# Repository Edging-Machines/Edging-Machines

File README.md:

This repository is a hub of information for [Edging Detection](https://github.com/Edging-Machines/Edging-Machines/wiki/Terminology#edging-detection) and [Edging Machines](https://github.com/Edging-Machines/Edging-Machines/wiki/Terminology#edging-machine). 
To get started, check the [Quick Start Guide](https://github.com/Edging-Machines/Edging-Machines/wiki), read the [History of Edging Devices](https://github.com/Edging-Machines/Edging-Machines/wiki/History), or browse through the different projects.

For any questions or discussion, please visit the [official discord server for Edging Machines](https://discord.gg/EvYbZBf).

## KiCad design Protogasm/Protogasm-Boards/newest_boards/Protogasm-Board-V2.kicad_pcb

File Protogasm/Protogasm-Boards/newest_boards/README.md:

# Protogasm Board V3

## Changelog

- Solved the issue with the incorrectly positioned SW1. SW1 should now line up with the case correctly (if I did all my math correctly)
- After a ton of problem solving, figured out a place for the MPX5050GP which should allow it to be used on the board without modifying the board. The constraints that I was considering ended up on User.1 and User.2 layers for future reference. The best solution seemed to be having the pressure sensor rotated and placed in the area of the Arduino without a bunch of tall components, with the valve facing the cutout of the case.
- I had hoped to keep most positions in the same place for this update (just fixing SW1 and MPX5050GP), but after moving the MPX I was forced to essentially update the positions of nearly every component. Additionally, I took the liberty of moving the motor pins closer to the case cutout and also flipped them to the reverse side.

# Protogasm Board V2

## Changelog

- Recreated the PCB from the Protogasm-Board folder in Kicad with only very minor changes.
- The vast majority of components are exactly lined up with the existing board. I overlaid the existing board's Gerbers with the gerbers of the remake and adjusted positions until stuff matched exactly.
- The general components C1, D1, SW1, and R1 have slightly different footprints because I was using the Kicad builtin footprints. They aren't pixel perfect but still overall in the same positions.
- I didn't want to just have loose pins for the motor connections and neopixel connections so I created actual components for them, this means I had to move them so that's one thing that has changed significantly in this board.
- Added the Arduino mounting holes, mostly so that it will be easier to test alignment of this board and the case.
- Overall, the idea is that if someone wants to change the Protogasm-Board but doesn't want the other changes that I'd like to make, they could start from this commit.

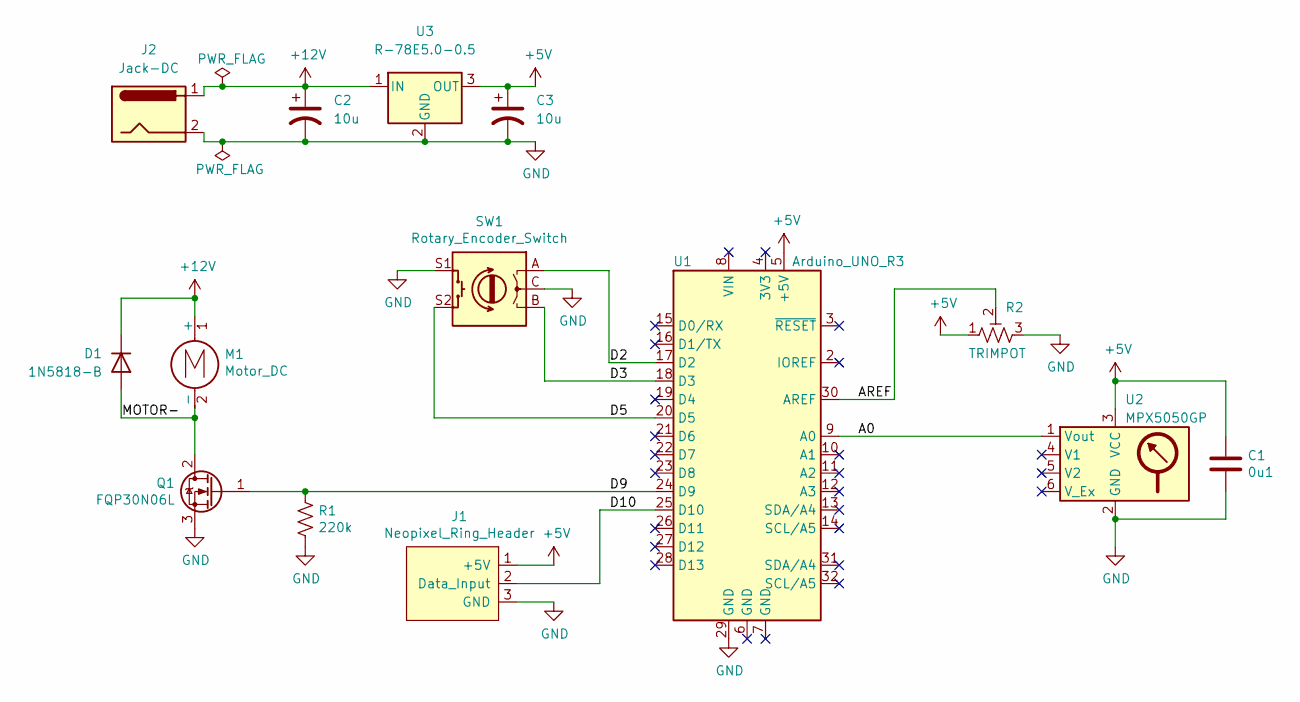
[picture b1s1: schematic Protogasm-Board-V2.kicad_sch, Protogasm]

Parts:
C1: 0u1; C_Disc_D5.0mm_W2.5mm_P2.50mm
C2, C3: 10u; CP_Radial_D5.0mm_P2.50mm
D1: 1N5818-B; D_A-405_P7.62mm_Horizontal
J1: Neopixel_Ring_Header; Neopixel_Ring_WirePins
J2: Jack-DC; 2.1mm DC Barrel Jack
M1: Motor_DC; Motor_DC_WirePins
Q1: FQP30N06L; TO-220-3_Horizontal_TabDown
R1: 220k; R_Axial_DIN0207_L6.3mm_D2.5mm_P7.62mm_Horizontal
R2: TRIMPOT; uxcell_TRIMPOT
SW1: Rotary_Encoder_Switch; RotaryEncoder_Alps_EC12E-Switch_Vertical_H20mm
U1: Arduino_UNO_R3; Arduino_UNO_R3_WithMountingHoles
U2: MPX5050GP
U3: R-78E5.0-0.5; Converter_DCDC_RECOM_R-78E-0.5_THT

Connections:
+5V: C1.1, C3.1, J1.1 (+5V), R2.1, U1.5 (+5V), U2.3 (VCC), U3.3 (OUT)
+12V: C2.1, D1.1 (K), J2.1, M1.1 (+), U3.1 (IN)
/A0: U1.9 (A0), U2.1 (Vout)
/AREF: R2.2, U1.30 (AREF)
/D2: SW1.A, U1.17 (D2)
/D3: SW1.B, U1.18 (D3)
/D5: SW1.S2, U1.20 (D5)
/D9: Q1.1 (G), R1.1, U1.24 (D9)
/D10: J1.2 (Data_Input), U1.25 (D10)
/MOTOR-: D1.2 (A), M1.2 (-), Q1.2 (D)
GND: C1.2, C2.2, C3.2, J1.3 (GND), J2.2, Q1.3 (S), R1.2, R2.3, SW1.C, SW1.S1, U1.29 (GND), U2.2 (GND), U3.2 (GND)

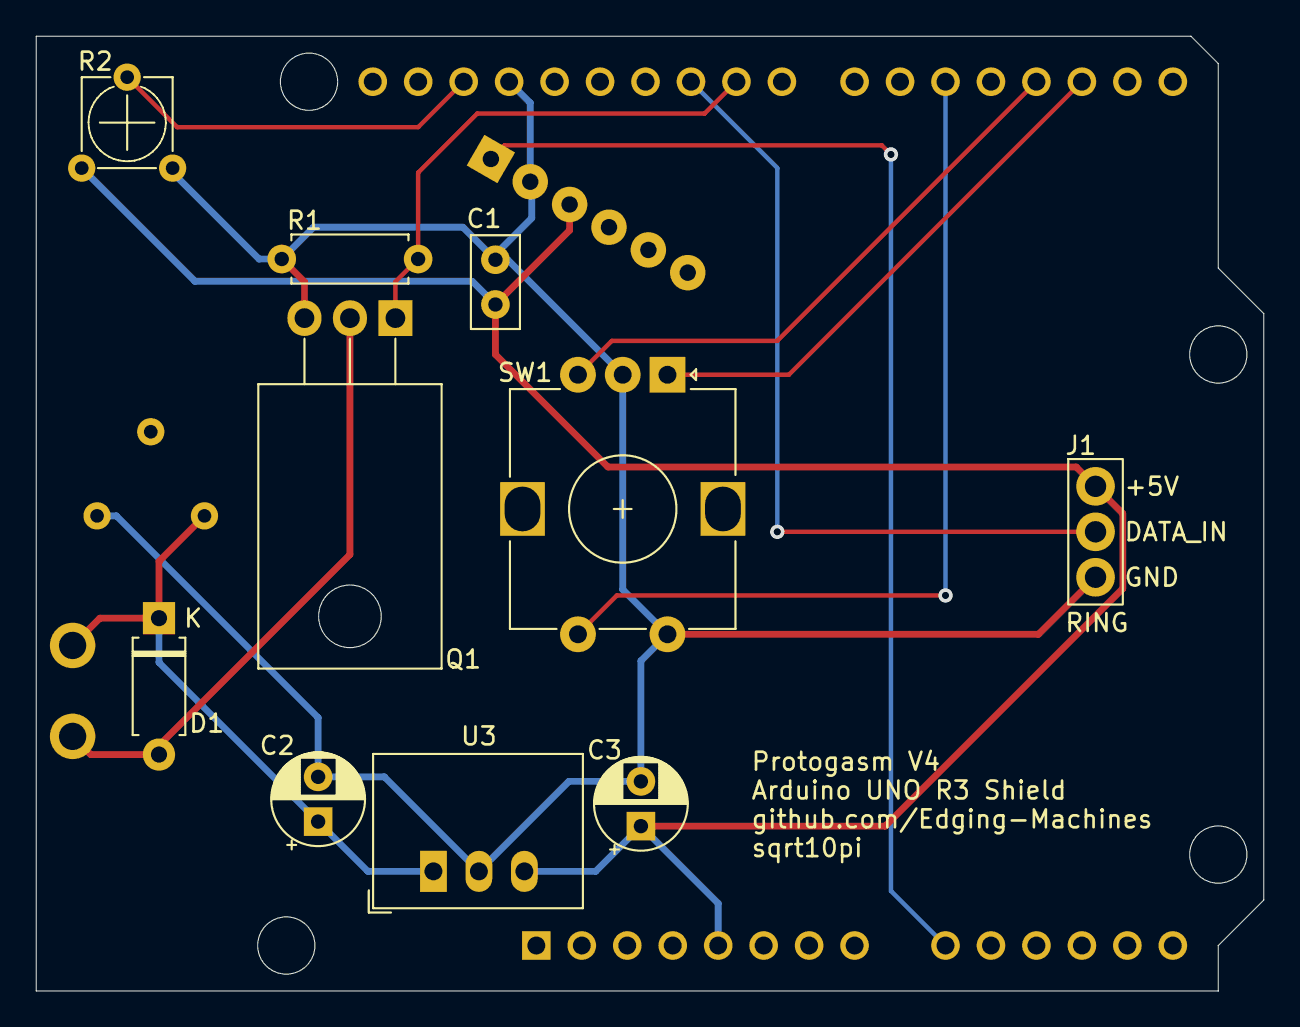
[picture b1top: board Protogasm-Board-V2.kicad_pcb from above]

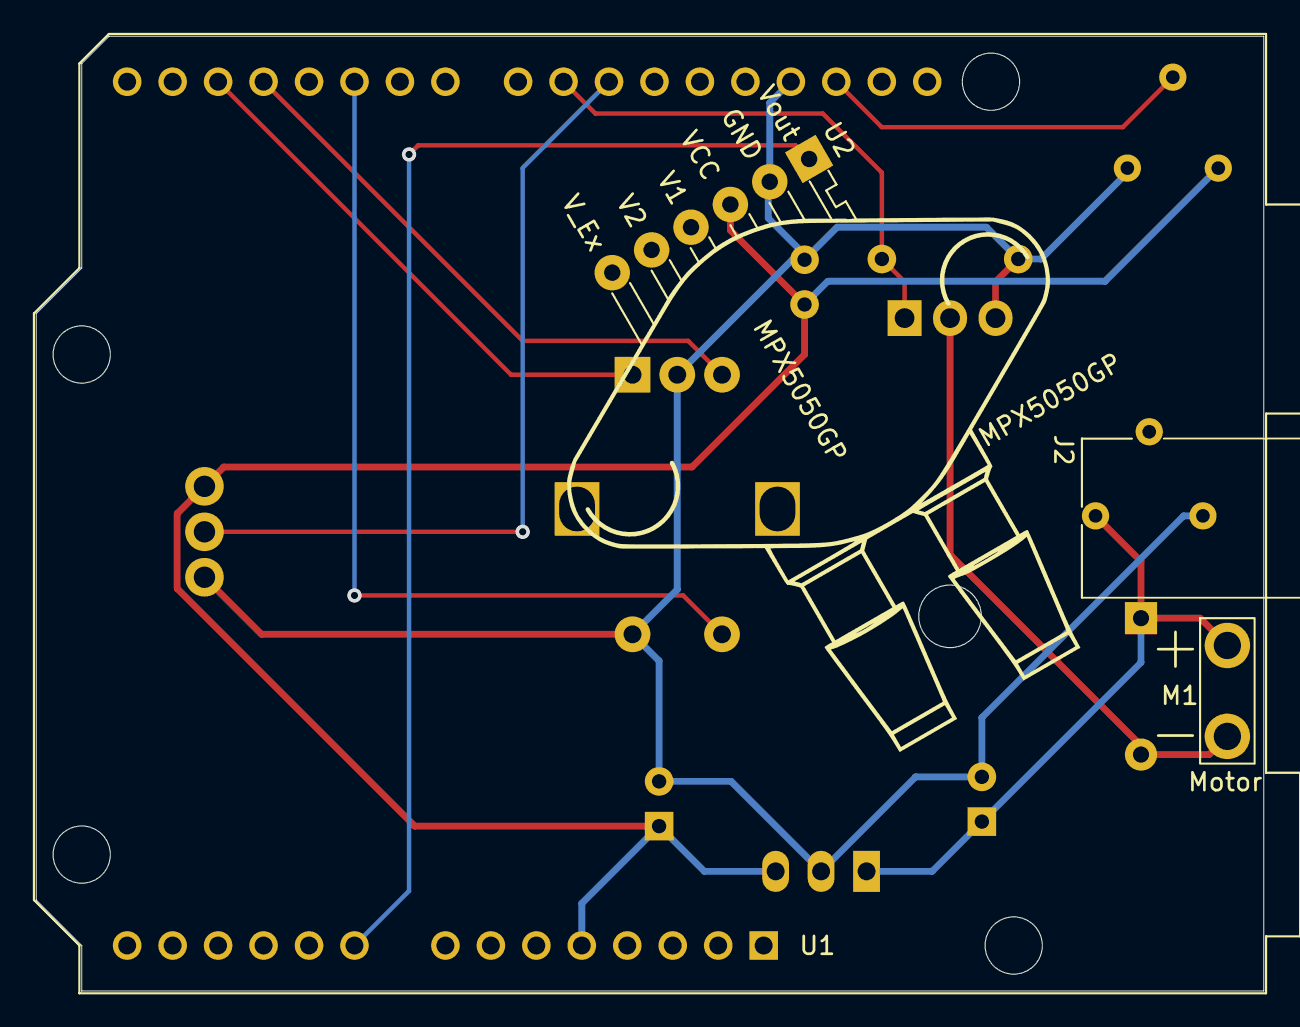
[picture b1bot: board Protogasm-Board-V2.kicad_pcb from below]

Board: 2 copper layers, 68.6 x 53.3 mm, 14 parts (4 on the bottom side), 11 nets.

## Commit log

2021-02-24 Added backup of nogasm repo
2021-02-24 Added protogasm repo backup
2021-02-24 Added nogasm wifi repo
2021-02-24 in progress
2021-02-24 added nogasm-wifi
2021-02-24 rename
2021-02-24 renamed
2021-02-24 gitignore
2021-02-24 fixed subrepo
2021-02-24 added nogasm and protogasm as submodules
2021-02-24 fix submodules
2021-02-24 Added EOM pressure shield repo
2021-02-24 test
2021-02-24 Remaking submodules
2021-02-24 adding submodules
2021-02-24 finished adding submodules
2021-02-24 added more protogasm info
2021-02-24 protogasm updates
2021-02-24 protogasm images
2021-02-24 added eom folder
2021-03-06 updates to better algorithm code
2021-11-23 added data
    added data
2021-12-03 Add another set of protogasm board images
    This is my first iteration of the board. Had some ideas while building this and might make a second version soon.
2022-07-15 added new protogasm board pcbs
